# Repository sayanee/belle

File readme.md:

# 🛎 belle

> Door bell with a buzzer and notification to IFTTT.

## Manufacture

1. Open [hardware](hardware) with [KiCad](http://kicad-pcb.org/)
1. Buy [Bill of Materials](bill_of_materials.csv)

## Getting started

### Flash the firmware

1. Ensure the batteries are not connected yet!
1. Short the 2 header pins on `P4` for boot mode
1. Connect an FTDI chip to `P3`
1. Connect the other end of the FTDI chip to the laptop via USB

1. Open Arduino IDE with the following configuration

1. Flash the [final firmware](firmware/belle.io) to the board
1. Remove the FTDI chip and the remove the shorted header pins of `P4`

### IFTTT

1. Configure IFTTT with [Webhooks](https://ifttt.com/maker_webhooks) and [Notification](https://ifttt.com/if_notifications) channels to Receive a web request
1. Put the event name as `bell_pressed`

1. Download the IFTTT app on mobile as well
1. Note the IFTTT key on the [maker_webhooks settings page](https://ifttt.com/services/maker_webhooks/settings)

### Connect your door bell

1. Connect 3 AA batteries
1. Ensure the blue on-board LED is blinking fast
1. Connect your actual door bell to `P2` connectors
1. Mount it up on the wall

1. Connect to WiFi access point with SSID `Belle XXXX` and password `beautyandthebeast` on mobile / laptop
1. Visit page <http://belle.local>
1. Fill in `SSID`, `Password` and `IFTTT Key`

1. Wait for the LED to stop blinking
1. Press the 🛎
1. You should hear the buzzer and get a mobile IFTTT notification as well :tada:

## References :books:

### Power savings

1. [Power Saving tips for the ESP8266](https://github.com/z2amiller/sensorboard/blob/master/PowerSaving.md)
1. [SparkFun 3.3V Step-Up Breakout - NCP1402](https://www.sparkfun.com/products/10967)
1. [Sleeping the ESP8266](http://www.esp8266.com/wiki/doku.php?id=esp8266_power_usage)
1. [Reddit: How to actually run an ESP8266 for months on AA batteries](https://www.reddit.com/r/esp8266/comments/4gmkfl/how_to_actually_run_an_esp8266_for_months_on_aa/)
1. [Battery Powered ESP8266 IoT – Temperature Sensor](http://homecircuits.eu/blog/battery-powered-esp8266-iot-logger/)
1. [ESP8266 Sensor runs 17 days on a coin cell](https://www.youtube.com/watch?v=IYuYTfO6iOs)
1. [wifiwebservers - ESP8266 with 2AA batteries](http://www.arduinesp.com/wifiwebserver)
1. [Simple Authentication](https://github.com/esp8266/Arduino/blob/4897e0006b5b0123a2fa31f67b14a3fff65ce561/libraries/ESP8266WebServer/examples/SimpleAuthentification/SimpleAuthentification.ino)
1. [Debouncing circuit](http://www.ganssle.com/debouncing-pt2.htm)

### Flashing

1. [Programming ESP12](http://glyncowles.blogspot.sg/2015/07/programming-and-running-esp12-e.html)
1. [Troubleshooting flashing](https://learn.sparkfun.com/tutorials/esp8266-thing-hookup-guide/discuss#comment-55a05571ce395f88538b4567)
1. [NodeMCU modes](https://raw.githubusercontent.com/nodemcu/nodemcu-devkit/master/Documents/NODEMCU_DEVKIT_SCH.png)

## Tools :radio:

1. [simple calculator for estimating a (LiPo) battery's life](http://battery-life.of-things.de/battery-life-calculator.php)
1. [Encode to Base64 format](https://www.base64encode.org/)
1. [Electronics circuit simulator](http://www.falstad.com/circuit/)
1. [Circuit calculator](http://circuitcalculator.com/)

## Credits :pray:

:star: Big thanks to [Chinmay](https://chinmay.audio/), [Adnan](https://github.com/catmaker), [Kenneth](https://github.com/kennethlimcp), [Shan](https://twitter.com/shannietron), [Baoshi](https://twitter.com/ba0sh1) for prototyping, feedback, verifications and soldering :star:

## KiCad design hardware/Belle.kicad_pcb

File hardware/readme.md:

# hardware continuity checklist

> Designed PCB layout with [KiCad](http://kicad-pcb.org/)

A list of connectivity checks after soldering

## Vcc (3.3V) - front

Reference: ESP8266 `Vcc` pin

- [x] `R3`, `R6`, `R7`, `R8`
- [x] `C2`, `C3`
- [x] `SP1` long pin
- [x] `P1` pin `1`
- [x] `U1` pin `6`
- [x] `U3`pin `5`

### Ground - back

Reference: ESP8266 `GND` pin

- [x] `R1`, `R5`
- [x] `C1`, `C2`, `C3`, `C4`, `C5`, `C6`, `C7`
- [x] `P2` Bell connector
- [x] `P3` FTDI connector
- [x] `P4` Boot jumper

## 5V

Reference: `P3` FTDI connector `5V`

- [x] `P2`
- [x] `C4`, `C7`
- [x] `U3` pins `1` and `3`

## Shorted pins?

- [x] `U1`, `U2` ESP8266, `U3`
- [x] `SP1`
- [x] `P1`, `P2`, `P3`, `P4`

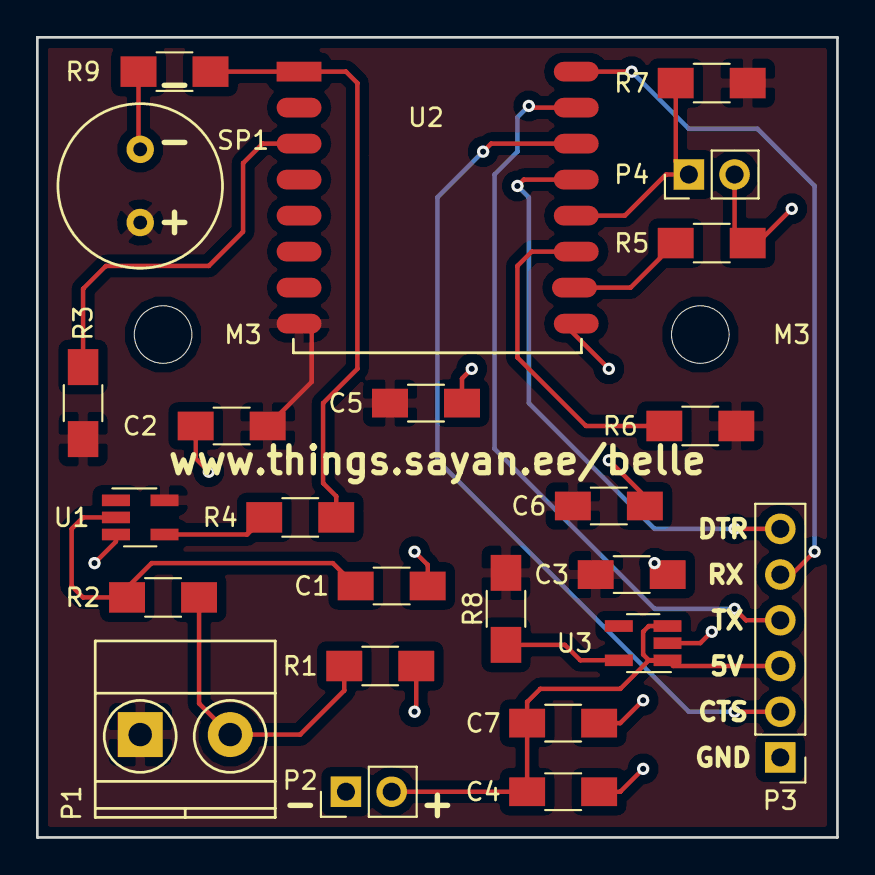
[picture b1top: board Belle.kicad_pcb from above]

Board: 2 copper layers, 44.4 x 44.5 mm, 26 parts (0 on the bottom side), 17 nets.

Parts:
C1, C3, C7: 1u; C_1206_HandSoldering
C2, C4, C6: DNP; C_1206_HandSoldering
C5: 10u; C_1206_HandSoldering
M3, M3#2: MountingHole_3.2mm_M3
P1: Bell CONN; TerminalBlock_Pheonix_MKDS1.5-2pol
P2: Battery CONN; Pin_Header_Straight_1x02_Pitch2.54mm
P3: FTDI Flashing CONN; Pin_Header_Straight_1x06_Pitch2.54mm
P4: Boot JUMPER; Pin_Header_Straight_1x02_Pitch2.54mm
R1: 22k; R_1206_HandSoldering
R2: 47k; R_1206_HandSoldering
R3, R5, R6, R7: 10K; R_1206_HandSoldering
R4, R8, R9: 0R; R_1206_HandSoldering
SP1: BUZZER; prosignal_buzzer
U1: 74AHC1G14; SOT-23-5_HandSoldering
U2: ESP-12; ESP-12F-SMD
U3: AP2112; SOT-23-5_HandSoldering

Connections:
+3V3: C2.2, C3.1, C5.2, C6.1, P1.1, R3.2, R6.1, R7.1, R8.2, SP1.2, U1.5, U2.8
/5V: C4.2, C7.2, P2.2, P3.3, U3.1, U3.3
/CTS: P3.2, U2.14
/DTR: P3.6, U2.13
/RX: P3.5, U2.16
/TX: P3.4, U2.15
GND: C1.2, C2.1, C3.2, C4.1, C5.1, C6.2, C7.1, P2.1, P3.1, P4.2, R1.1, R5.2, U1.3, U2.9, U3.2
unnamed: C1.1, R2.1, U1.2
unnamed: P1.2, R1.2, R2.2
unnamed: P4.1, R7.2, U2.12
unnamed: R3.1, U2.3
unnamed: R4.1, R9.1, U2.1
unnamed: R4.2, U1.4
unnamed: R5.1, U2.10
unnamed: R6.2, U2.11
unnamed: R8.1, U3.5
unnamed: R9.2, SP1.1

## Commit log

2017-03-05 fix breadboard.JPG image name link
2017-03-05 fix belle.ino file name
2017-03-05 add Schmitt trigger data sheet
2017-03-05 fix file extension from io to *.ino
2017-03-05 remove BOM heading until it is there
2017-03-05 include ESP8266 library
2017-03-09 add C1 datasheet
2017-03-15 add more datasheets
2017-03-15 fix list format
2017-03-19 add gerbers
2017-03-19 remove datasheet external links
2017-03-19 edit schematic
2017-03-19 fix images
2017-03-19 edit layout
2017-03-19 fix ordered list format
2017-03-19 regenerated gerbers
2017-03-19 edit layout. close #1
2017-03-20 add thanks
2017-03-20 add more thanks
2017-03-20 add notes to the schematic. close #4
2017-03-20 fix English
2017-03-21 rename speaker to buzzer. close #9
2017-03-21 add new datasheet for LDO
2017-03-21 add ESP12 module in BOM and datasheet. close #13
2017-03-21 add links for debouncing and simulation
2017-04-14 add circuit simulator as a tool
2017-04-16 add flashing mode instructions for ESP8266
2017-04-17 add more photos
2017-04-18 amend the datasheet name from distributor to manufacturer
2017-04-19 interchange bell connectors #6
2017-04-19 add code for simple interrupt from sleep
2017-04-19 connect to WiFi on waking up
2017-04-20 add code to ping IFTTT upon wakeup
2017-04-20 add photo with Schmitt trigger
2017-04-20 format images
2017-04-22 add commonly referenced diagrams
2017-04-24 rename file
2017-04-25 add 10k resistor between RESET and Smidth Trigger output
2017-05-01 add extra capacitors. close #3
2017-05-01 arrange flashing connector as default FTDI pin. close #5
2017-05-02 re-generate net list based on new schematic
2017-05-03 generate bill of materials
2017-05-03 rename datasheet accordingly to BOM
2017-05-03 rename resistors in order of schematic placement
2017-05-04 initial rat's nest. #2 #10
2017-05-09 layout PCB
2017-05-09 adjust decoupling capacitors
2017-05-09 add labels for battery connecter
2017-05-09 add gerber files
2017-05-09 add board info on the silkscreen. close #16
2017-05-10 add dfm tweaks. #18
2017-05-10 modifiec PCB
2017-05-14 add new gerber generated files
2017-05-14 add iteration
2017-05-14 fix markdown table format
2017-06-12 add bom as csv file
2017-06-13 move the mounting hoel slightly. close #21
2017-06-13 edit bom
2017-06-17 correct labelling of ground and power
2017-07-10 add blinky firmware
2017-07-10 connect with wifi
2017-07-12 add annotations for buzzer
2017-07-13 update screenshot with buzzer pin annotations
2017-07-25 add sleep and wakeup interrupt
2017-07-25 add firmware to send HTTP POST to IFTTT on bell press
2017-07-26 send http post request only on waking up from deep sleep
2017-07-26 fix spacing
2017-07-26 remove unused pinMode for LED_BUILTIN
2017-07-27 add serial console messages
2017-07-28 create input fields for initial configuration
2017-07-28 connect to ssid and password via web form
2017-07-28 better console messages
2017-07-29 better logs
2017-07-30 erase wifi credentials
2017-07-30 configure wifi if no credential is present
2017-07-30 abstract into functions
2017-07-31 add error checking for http get to ifttt
2017-07-31 add first time setup code
2017-08-09 add read and write to eeprom
2017-08-12 add wiring continuity checklist
2017-08-12 fix format
2017-08-12 check each list
2017-08-12 add shorted pin check
2017-08-13 fix IFTTT key reading after reset
2017-08-13 refactor pin 2 to a #define
2017-08-13 abstract away go to sleep function
2017-08-13 clean up serial prints
2017-08-13 remove more serial prints
2017-08-13 update bom prices
2017-08-13 update instructions
2017-08-13 fix image name
2017-08-14 add test firmwarefor blinky, wifi and sleeping
2017-08-14 add test for wakeup on reset
2017-08-15 refactor test code for minor changes
2017-08-15 add todo erase SSID and password for test firmware
2017-08-15 add step to erase stored SSID and password
2017-08-15 differentiate between wakeup from deep sleep or start
2017-08-15 add consistent baud rate of 115200
2017-08-15 add 3 0Ω resistors to schematic and bom
2017-08-20 Rename R4 to 0R
2017-08-20 Add R9 0R resistor to layout
2017-08-20 Save KiCad
2017-08-21 Update new layout and schematic diagrams
2017-08-21 Generate GERBERS
2017-08-27 Remove through hole for ESP-12F module. close #22
2017-08-27 Save project
2017-08-27 Save KiCad project
2017-09-02 Add instructions to press the button to test
2017-09-02 Add new lines in print statements
2017-09-03 Send to IFTTT after multiple short presses that detects reset from external system
2017-09-17 Add hardware connectivity instructions
